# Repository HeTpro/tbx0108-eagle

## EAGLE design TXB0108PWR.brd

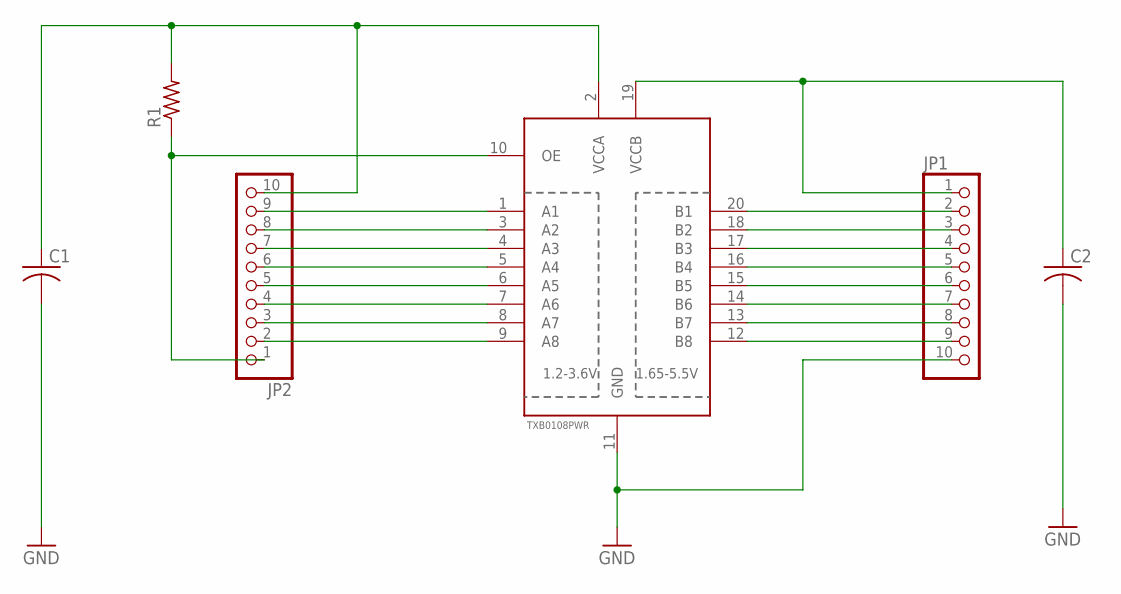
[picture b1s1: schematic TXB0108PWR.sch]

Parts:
C1, C2: C-USC0603; C0603
JP1, JP2: PINHD-1X10; 1X10
R1: R-US_R0603; R0603
U$1: TXB0108PWR

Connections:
B1: JP1.2, U$1.20 (B1)
B2: JP1.3, U$1.18 (B2)
B3: JP1.4, U$1.17 (B3)
B4: JP1.5, U$1.16 (B4)
B5: JP1.6, U$1.15 (B5)
B6: JP1.7, U$1.14 (B6)
B7: JP1.8, U$1.13 (B7)
B8: JP1.9, U$1.12 (B8)
GND: C1.2, C2.2, JP1.10, U$1.11 (GND)
unnamed: JP2.9, U$1.1 (A1)
unnamed: JP2.8, U$1.3 (A2)
unnamed: JP2.7, U$1.4 (A3)
unnamed: JP2.6, U$1.5 (A4)
unnamed: JP2.5, U$1.6 (A5)
unnamed: JP2.4, U$1.7 (A6)
unnamed: JP2.3, U$1.8 (A7)
unnamed: JP2.2, U$1.9 (A8)
OE: JP2.1, R1.1, U$1.10 (OE)
VCCA: C1.1, JP2.10, R1.2, U$1.2 (VCCA)
VCCB: C2.1, JP1.1, U$1.19 (VCCB)

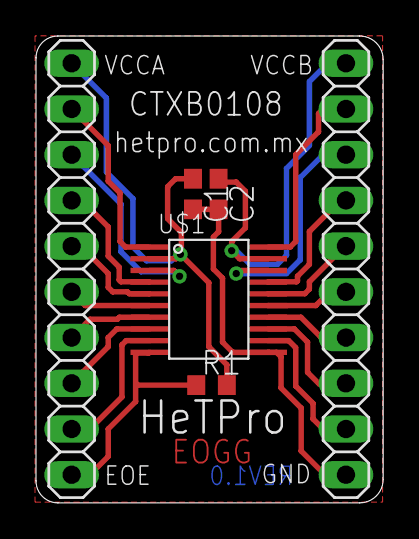
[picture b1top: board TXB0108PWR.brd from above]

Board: 2 copper layers, 19.3 x 25.9 mm, 6 parts (0 on the bottom side), 20 nets.

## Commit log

2015-04-22 :octocat: Added .gitattributes & .gitignore files
2015-04-22 Archivos
